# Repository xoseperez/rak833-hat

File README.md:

# RAK833 Hat for Raspberry Pi

This repository contains the PCB design for a hat and installation procedure to use a RAK833 MiniPCI-E module with a Raspberry Pi.

## Licenses

The installation procedure is based on the [ttn-zh](http://github.com/ttn-zh) installation procedure for the [IMST iC880a](https://github.com/ttn-zh/ic880a-gateway) module and thus uses the same GPL-3.0 license.

The PCB design and layout is licensed under CC-SA-BY-4.0 International.

License files are available under each folder.

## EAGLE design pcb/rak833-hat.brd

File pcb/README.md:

# RAK833 Hat

## Bill of materials

This is the bill of materials for the RAK833 Hat for Raspberry Pi.

You will need an SPI or SPI/USB (more expensive) RAK833 concentrator. RAK Wireless sells them on their Aliexpress store, there is no other place to buy it from IFAIK.

|Item|Qty|Datasheet|Reference|Unit price (*)|
| :--- | :---: | :---: | :---: | :---: |
| RAK833 PCB (lead-free, buying 5 units) | 1 | | [PCBWay](https://www.pcbway.com/project/shareproject/RAK833_Raspberry_Pi_Hat_v0_1_20180529.html) | 3.8€ |
| RAK833 MiniPCI | 1 | [PDF](http://docs.rakwireless.com/en/RAK833%20PCIE%20LoRa%20Gateway/hardware%20design/RAK833%20LoRa%20Gateway%20DataSheet%20V1.3.pdf) | [Aliexpress (SPI-only)](https://www.aliexpress.com/item/RAK833-SPI-SX1301Chip-868-915MHz-Industrial-Grade-Mini-PCIe-LoRa-Gateway-Concentrator-Module-support-SPI-Interface/32887664396.html)<br />[Aliexpress (SPI & USB)](https://www.aliexpress.com/item/RAK833-SPI-USB-Industrial-Grade-Mini-PCIe-LoRa-Gateway-Concentrator-Module-SX1301-FT2232H-Chip-868-915MHz/32867370031.html) | 86.41€<br />103.87€ |
| Glass Fiber Antenna Gain 6dbm | 1 | | [Aliexpress](https://www.aliexpress.com/store/product/Glass-Fiber-Antenna-Gain-6dbm-Transmission-range-is-further-LoRa-Gateway-Antenna-with-433-470-868/2805180_32852314761.html) | 24.02€ |
| Molex MiniPCI-E 4.0H connector | 1 | [PDF](https://www.mouser.es/datasheet/2/276/480996701_sd-155861.pdf) | [Mouser (connector)](https://www.mouser.es/ProductDetail/538-67910-1002) <br /> [Mouser (latch)](https://www.mouser.es/ProductDetail/538-48099-5701) | 1.82€<br />1.07€ |
| Molex 47346-1001 microUSB connector | 1 | [PDF](https://www.mouser.es/datasheet/2/276/0473461001_IO_CONNECTORS-272892.pdf) | [Mouser](https://www.mouser.es/ProductDetail/538-47346-1001) | 0.55€ |
| AMS1117-3V3 | 1 | | [Aliexpress](https://www.aliexpress.com/item/10pcs-AMS1117-3-3-AMS1117-LM1117-1117-3-3V-1A-Voltage-Regulator/32348815272.html) | 0.03€ |
| 10uF 6.3V Tantalum Capacitors | 2 | [PDF](https://www.mouser.es/datasheet/2/40/tps-776850.pdf) | [Mouser](https://www.mouser.es/ProductDetail/581-TPSR106K006R1500) | 0.60€ |
| SMD DPDT switch | 1 | | [Aliexpress](https://www.aliexpress.com/item/5PCS-3-Position-6-Pins-DPDT-Panel-PCB-Mount-Mini-SMD-SMT-Slide-Switch-7x6x4mm/32553945435.html) | 0.69€ |
| SMD push button | 1 | | [Aliexpress](https://www.aliexpress.com/item/100PC-Lot-SMD-4-4-1-5MM-4X4X1-5MM-Tactile-Tact-Push-Button-Micro-Switch-Momentary/32623940621.html) | 0.01€ |
| Raspberry Pi 3 | 1 | | | ~30€ |
| 20x2 2.54pitch header for Raspberry Pi | 1 | | | ~0.25€ |
| **TOTAL (SPI-only version)** | | | | **~150€** |

(*) Prices are shown here for reference. They might change depending on your supplier. They also change depending on the number of units you buy. All prices excluding shipping or customs.

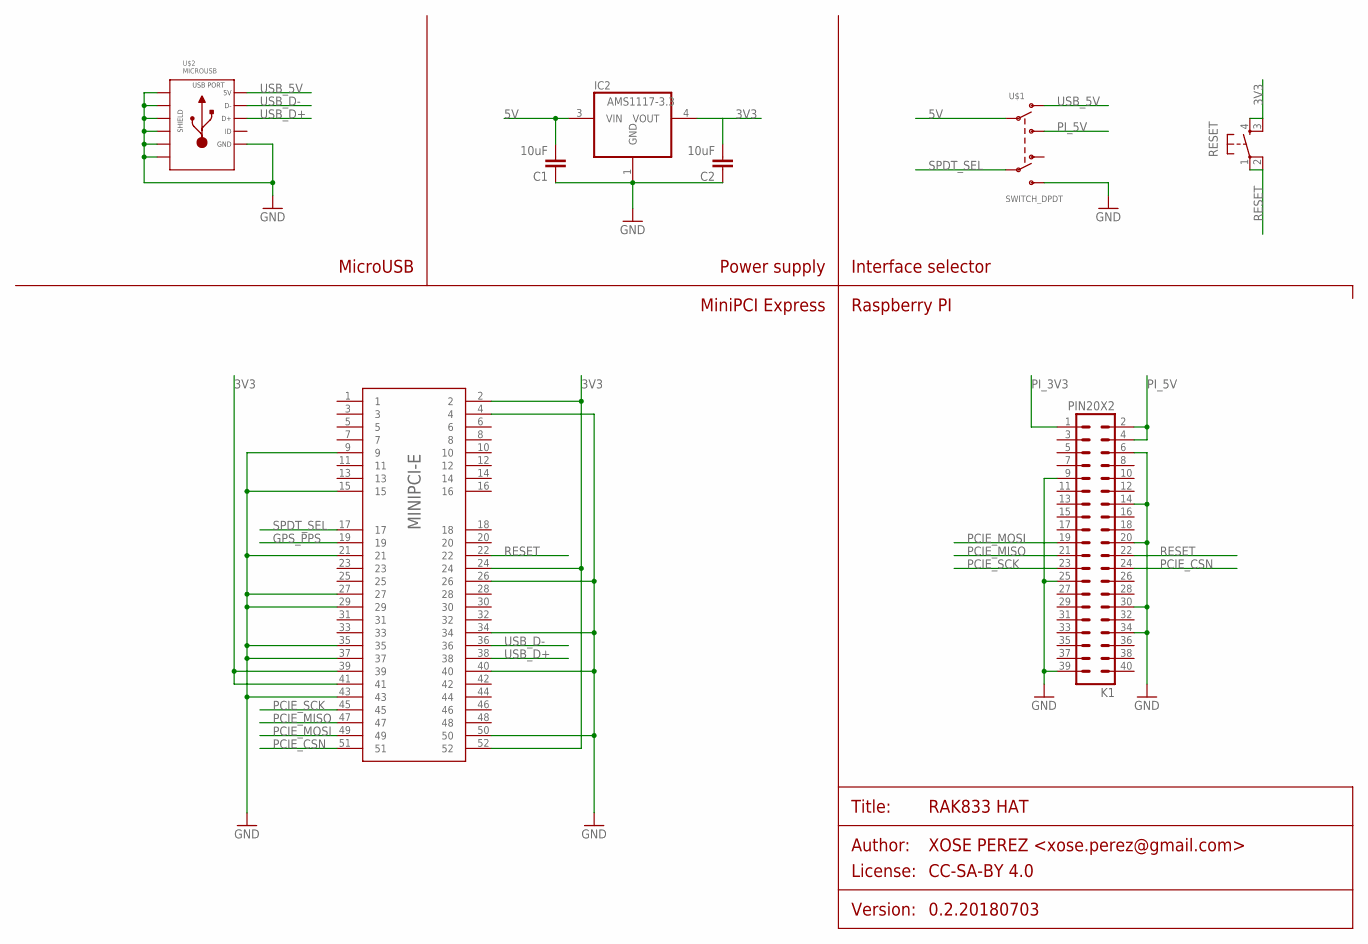
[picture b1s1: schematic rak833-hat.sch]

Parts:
C1, C2: 10uF; 0805
IC2: AMS1117-3.3; SOT223
K1: PIN20X2; PIN_20X2
MINIPCI-E: MINI-PCIE-RAW; 67910-MINI-PCIE
RESET: TACTILE_BUTTON_SMD; TACTILE-BUTTON-SMD
U$1: SWITCH_DPDT; SWITCH_DPDT_SMD
U$2: MICROUSB; MICROUSB-MOLEX-47346-0001

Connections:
3V3: C2.2, IC2.4 (VOUT), MINIPCI-E.2, MINIPCI-E.24, MINIPCI-E.39, MINIPCI-E.41, MINIPCI-E.52, RESET.3 (SWB2), RESET.4 (SWA2)
5V: C1.2, IC2.3 (VIN), U$1.A1 (P1)
GND: C1.1, C2.1, IC2.1 (GND), K1.6, K1.9, K1.14, K1.20, K1.25, K1.30, K1.34, K1.39, MINIPCI-E.4, MINIPCI-E.9, MINIPCI-E.15, MINIPCI-E.21, MINIPCI-E.26, MINIPCI-E.27, MINIPCI-E.29, MINIPCI-E.34, MINIPCI-E.35, MINIPCI-E.37, MINIPCI-E.40, MINIPCI-E.43, MINIPCI-E.50, U$1.C2 (S2), U$2.GND, U$2.SLD1, U$2.SLD2, U$2.SLD3, U$2.SLD4, U$2.SLD5, U$2.SLD6
GPS_PPS: MINIPCI-E.19
PCIE_CSN: K1.24, MINIPCI-E.51
PCIE_MISO: K1.21, MINIPCI-E.47
PCIE_MOSI: K1.19, MINIPCI-E.49
PCIE_SCK: K1.23, MINIPCI-E.45
PI_3V3: K1.1
PI_5V: K1.2, K1.4, U$1.C1 (S1)
RESET: K1.22, MINIPCI-E.22, RESET.1 (SWA1), RESET.2 (SWB1)
SPDT_SEL: MINIPCI-E.17, U$1.A2 (P2)
USB_5V: U$1.B1 (O1), U$2.VCC (5V)
USB_D+: MINIPCI-E.38, U$2.D+
USB_D-: MINIPCI-E.36, U$2.D-

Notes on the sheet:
MiniPCI Express
Raspberry PI
Interface selector
Power supply
MicroUSB

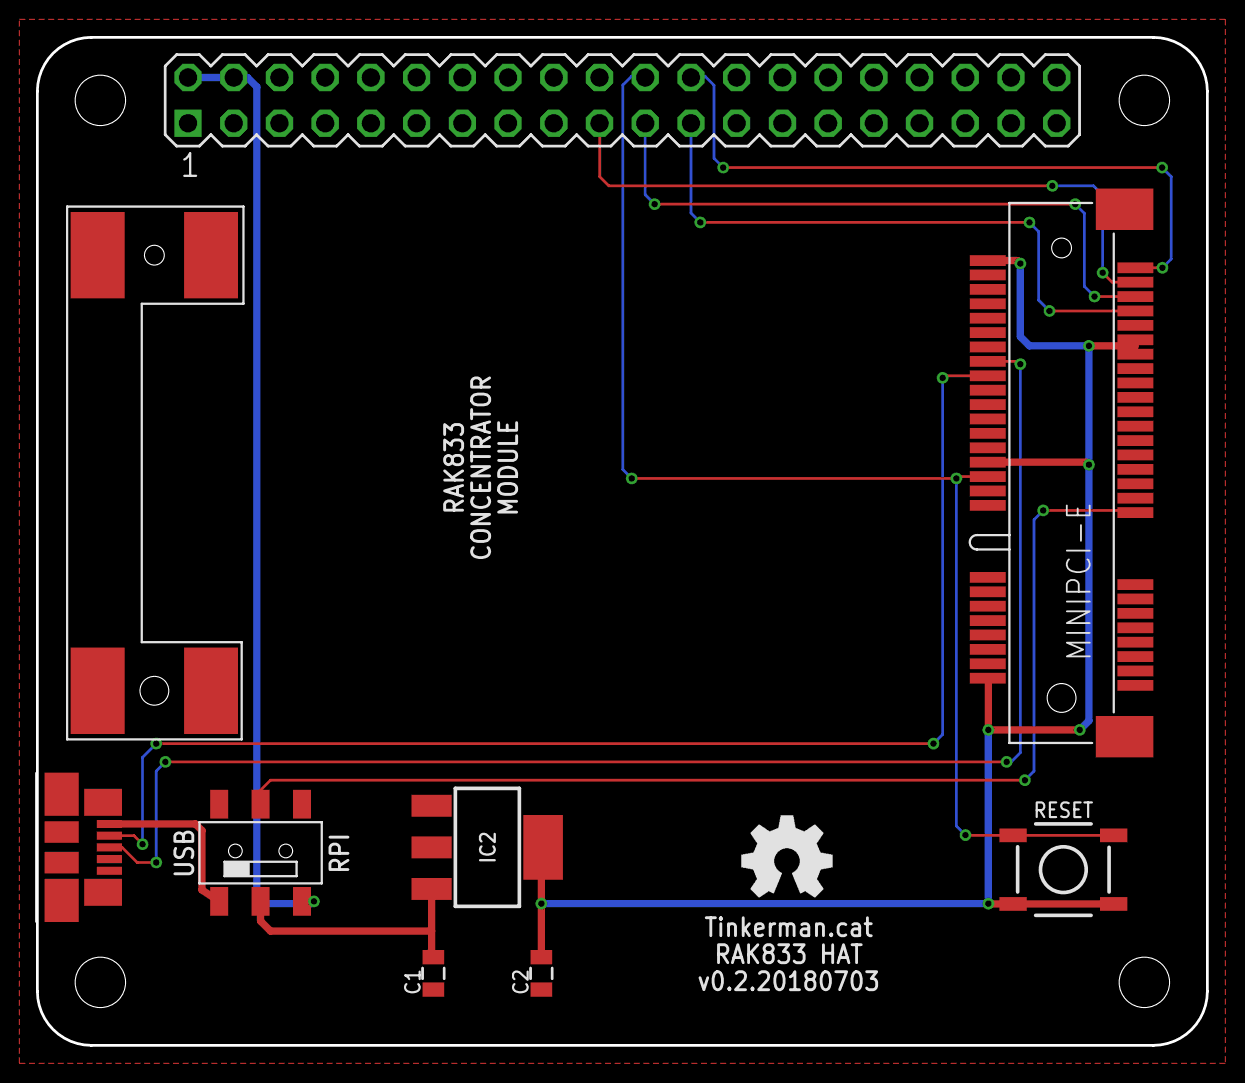
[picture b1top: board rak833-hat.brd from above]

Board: 2 copper layers, 65.0 x 56.0 mm, 8 parts (0 on the bottom side), 13 nets.

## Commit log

2018-07-02 PCB version 0.1.20180529
2018-07-03 Fixing switch footprint
2018-07-03 Licensed as CC-BY-SA-4.0 International
2018-07-03 Images and BOM
2018-07-03 Installation procedure
2018-07-03 Fix install branch
2018-07-03 Fix links
2018-07-03 Add references to original installation procedure for iC880a

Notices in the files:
pcb/rak833-hat.sch:
PROJECT_LICENSE: CC-SA-BY 4.0
parts and their libraries:
SparkFun-Aesthetics: Licensing: Creative Commons ShareAlike 4.0 International - https://creativecommons.org/licenses/by-sa/4.0
